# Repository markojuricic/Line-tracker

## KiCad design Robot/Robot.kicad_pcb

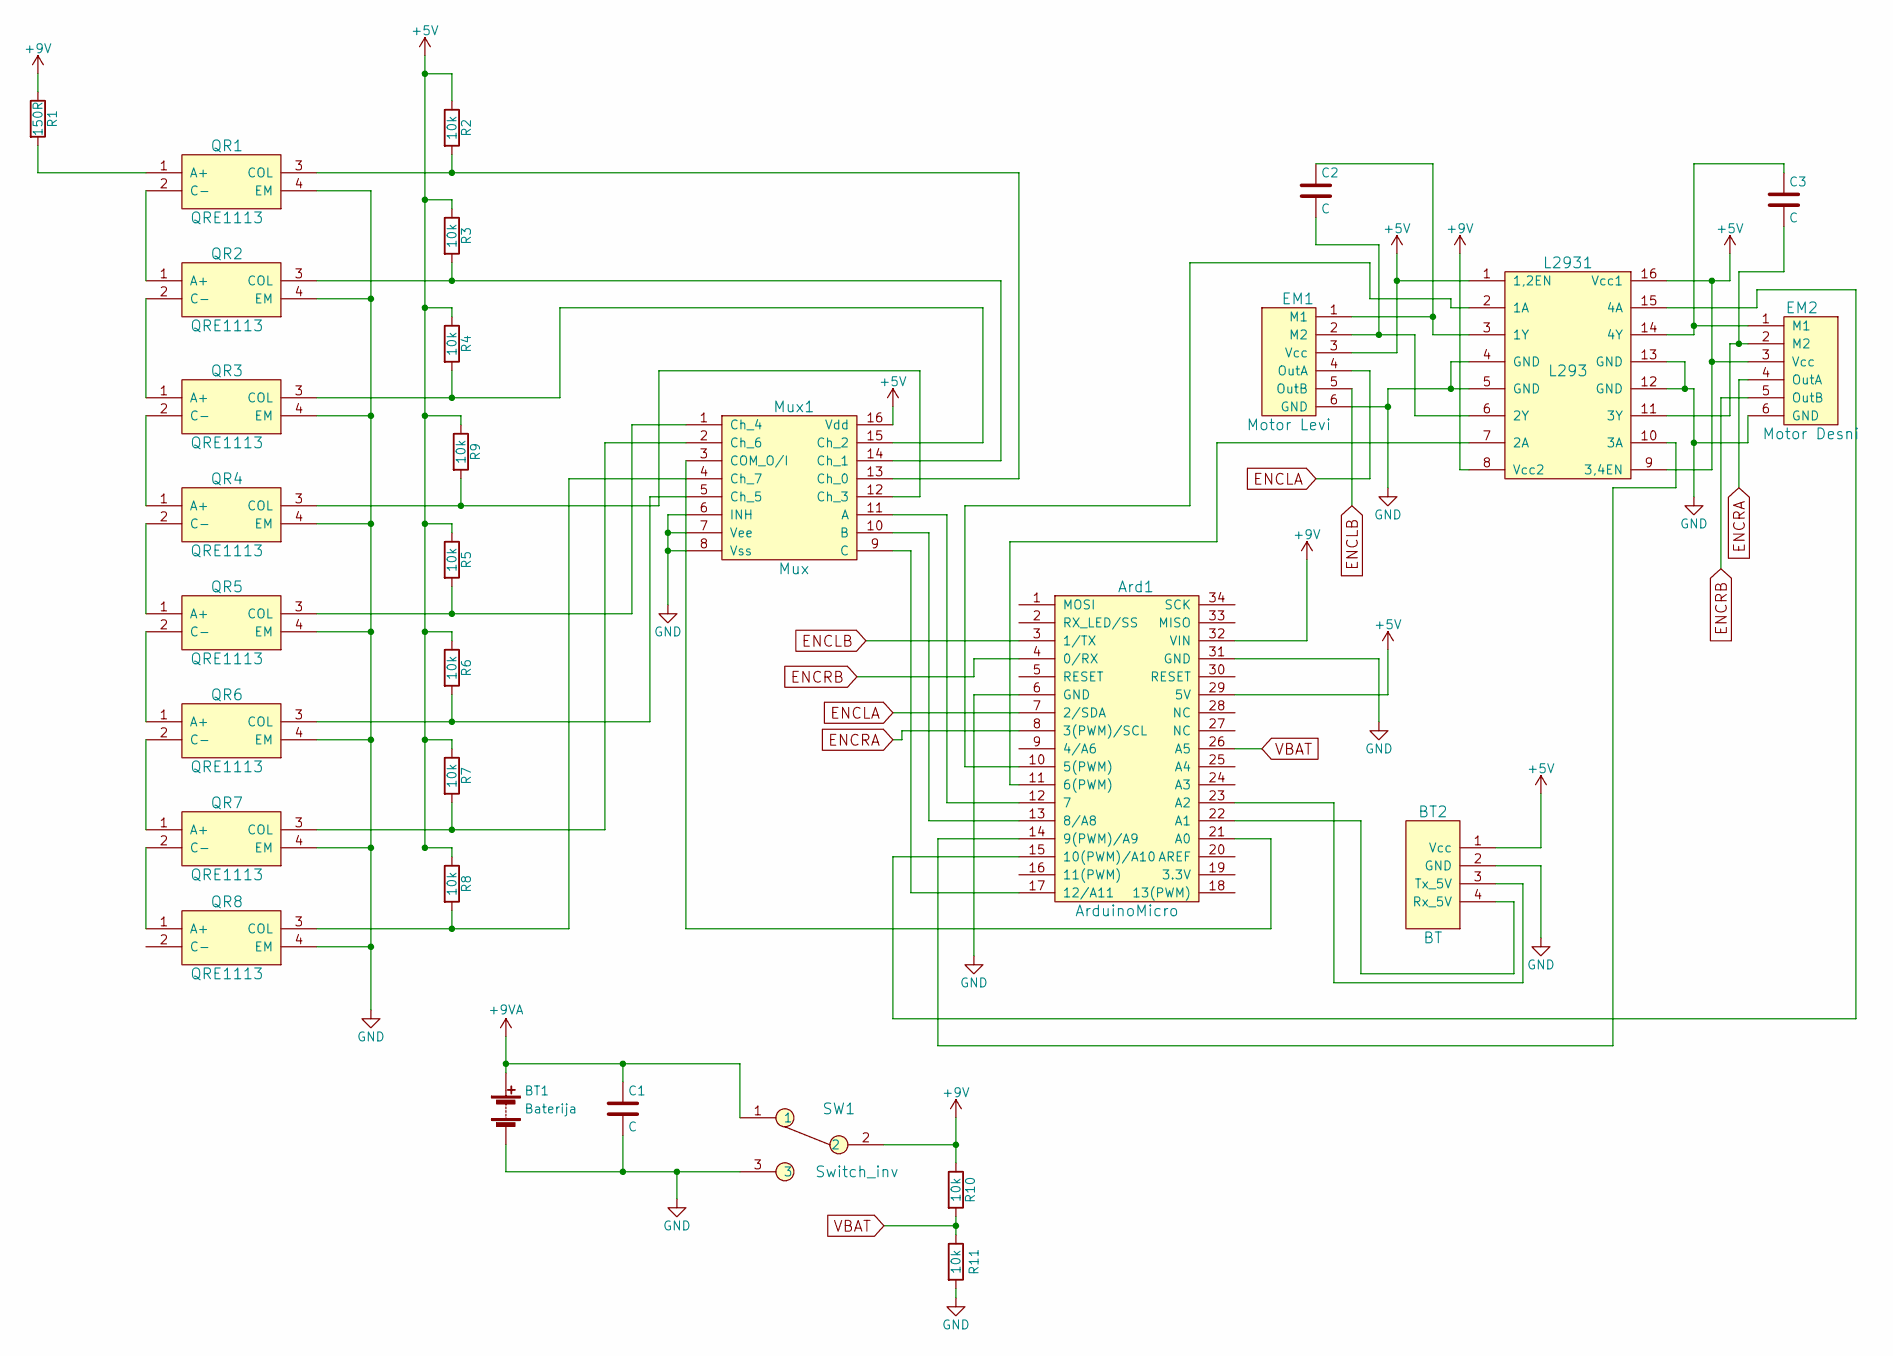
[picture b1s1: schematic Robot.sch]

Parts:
Ard1: ArduinoMicro; ARDUINO_MICRO_SHIELD
BT1: Baterija; Battery_holder_1291
BT2: BT; BT_Smirf
C1, C2, C3: C; C_0805_HandSoldering
EM1: Motor Levi; EM_holder
EM2: Motor Desni; EM_holder
L2931: L293
Mux1: Mux; Mux_8Ch
QR1, QR2, QR3, QR4, QR5, QR6, QR7, QR8: QRE1113; QRE1113GR
R1: 150R; R_0805_HandSoldering
R2, R3, R4, R5, R6, R7, R8, R9, R10, R11: 10k; R_0805_HandSoldering
SW1: Switch_inv; Switch

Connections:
+5V: Ard1.29 (5V), BT2.1 (Vcc), EM1.3 (Vcc), EM2.3 (Vcc), L2931.1 (1,2EN), L2931.9 (3,4EN), L2931.16 (Vcc1), Mux1.16 (Vdd), R2.1, R3.1, R4.1, R5.1, R6.1, R7.1, R8.1, R9.1
+9V: Ard1.32 (VIN), L2931.8 (Vcc2), R1.1, R10.1, SW1.2
+9VA: BT1.1 (+), C1.1, SW1.1
ENCLA: Ard1.7 (2/SDA), EM1.4 (OutA)
ENCLB: Ard1.3 (1/TX), EM1.5 (OutB)
ENCRA: Ard1.8 (3(PWM)/SCL), EM2.4 (OutA)
ENCRB: Ard1.4 (0/RX), EM2.5 (OutB)
GND: Ard1.6 (GND), Ard1.31 (GND), BT1.2 (-), BT2.2 (GND), C1.2, EM1.6 (GND), EM2.6 (GND), L2931.4 (GND), L2931.5 (GND), L2931.12 (GND), L2931.13 (GND), Mux1.6 (INH), Mux1.7 (Vee), Mux1.8 (Vss), QR1.4 (EM), QR2.4 (EM), QR3.4 (EM), QR4.4 (EM), QR5.4 (EM), QR6.4 (EM), QR7.4 (EM), QR8.4 (EM), R11.2, SW1.3
unnamed: Ard1.10 (5(PWM)), L2931.2 (1A)
unnamed: Ard1.11 (6(PWM)), L2931.7 (2A)
unnamed: Ard1.12 (7), Mux1.11 (A)
unnamed: Ard1.13 (8/A8), Mux1.10 (B)
unnamed: Ard1.14 (9(PWM)/A9), L2931.10 (3A)
unnamed: Ard1.15 (10(PWM)/A10), L2931.15 (4A)
unnamed: Ard1.17 (12/A11), Mux1.9 (C)
unnamed: Ard1.21 (A0), Mux1.3 (COM_O/I)
unnamed: Ard1.22 (A1), BT2.4 (Rx_5V)
unnamed: Ard1.23 (A2), BT2.3 (Tx_5V)
unnamed: C2.1, EM1.1 (M1), L2931.3 (1Y)
unnamed: C2.2, EM1.2 (M2), L2931.6 (2Y)
unnamed: C3.1, EM2.1 (M1), L2931.14 (4Y)
unnamed: C3.2, EM2.2 (M2), L2931.11 (3Y)
unnamed: Mux1.1 (Ch_4), QR5.3 (COL), R5.2
unnamed: Mux1.2 (Ch_6), QR7.3 (COL), R7.2
unnamed: Mux1.4 (Ch_7), QR8.3 (COL), R8.2
unnamed: Mux1.5 (Ch_5), QR6.3 (COL), R6.2
unnamed: Mux1.12 (Ch_3), QR4.3 (COL), R9.2
unnamed: Mux1.13 (Ch_0), QR1.3 (COL), R2.2
unnamed: Mux1.14 (Ch_1), QR2.3 (COL), R3.2
unnamed: Mux1.15 (Ch_2), QR3.3 (COL), R4.2
unnamed: QR1.1 (A+), R1.2
unnamed: QR1.2 (C-), QR2.1 (A+)
unnamed: QR2.2 (C-), QR3.1 (A+)
unnamed: QR3.2 (C-), QR4.1 (A+)
unnamed: QR4.2 (C-), QR5.1 (A+)
unnamed: QR5.2 (C-), QR6.1 (A+)
unnamed: QR6.2 (C-), QR7.1 (A+)
unnamed: QR7.2 (C-), QR8.1 (A+)
VBAT: Ard1.26 (A5), R10.2, R11.1

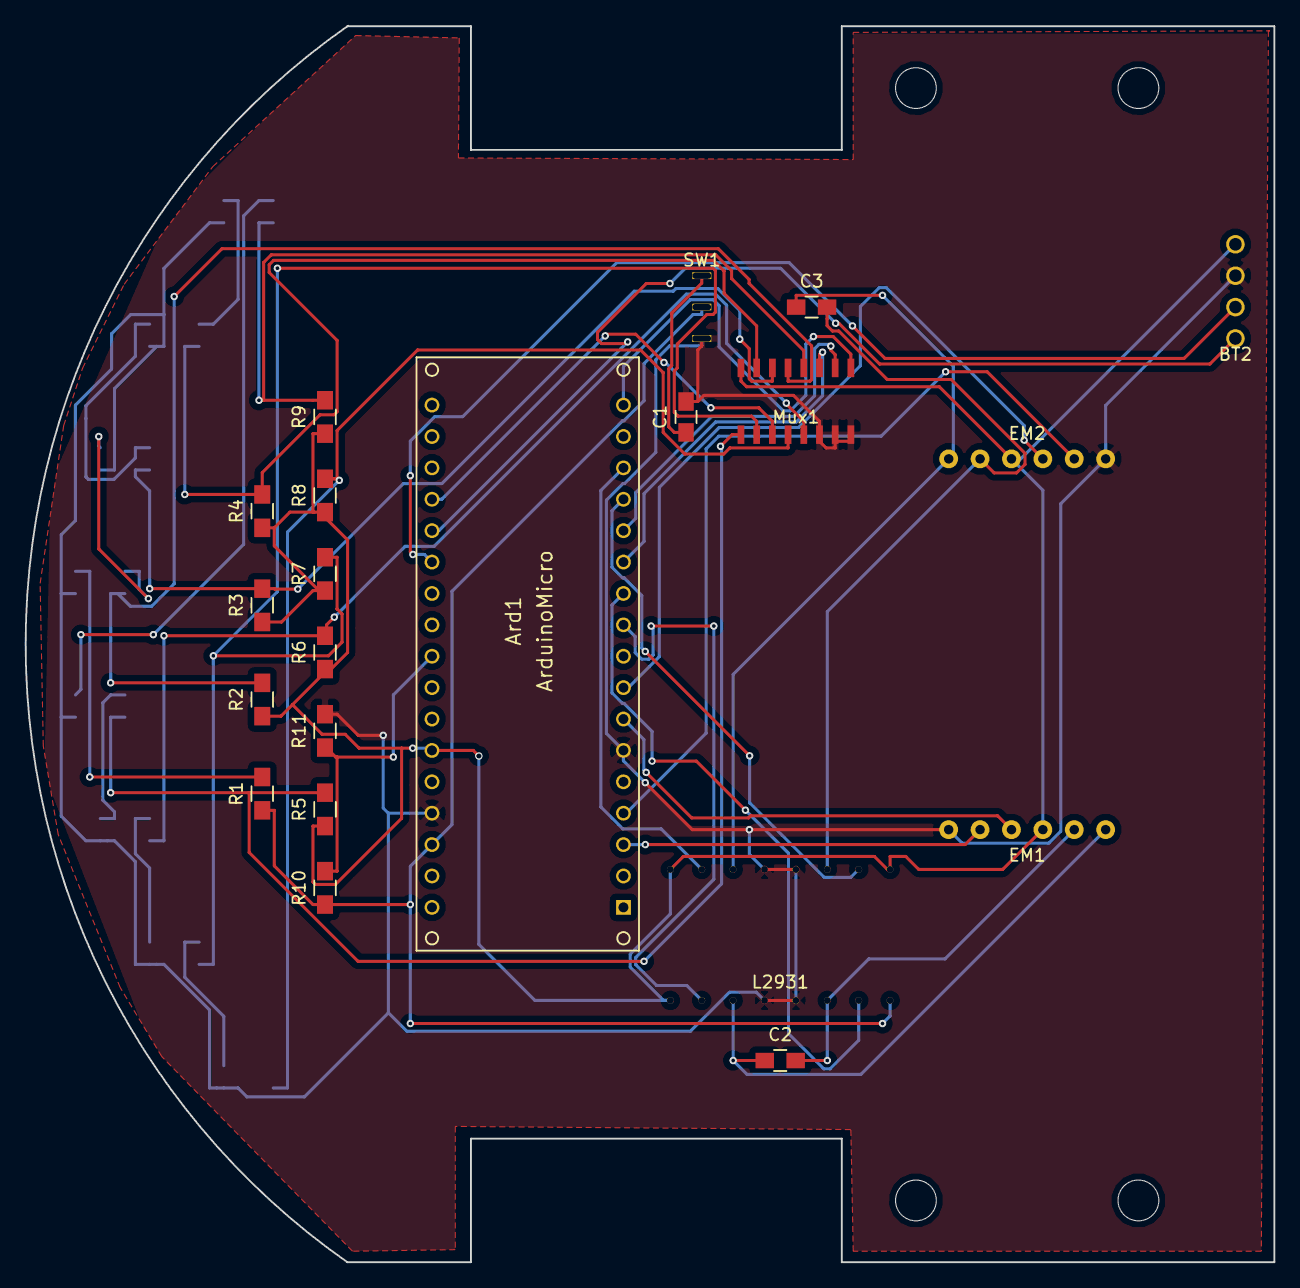
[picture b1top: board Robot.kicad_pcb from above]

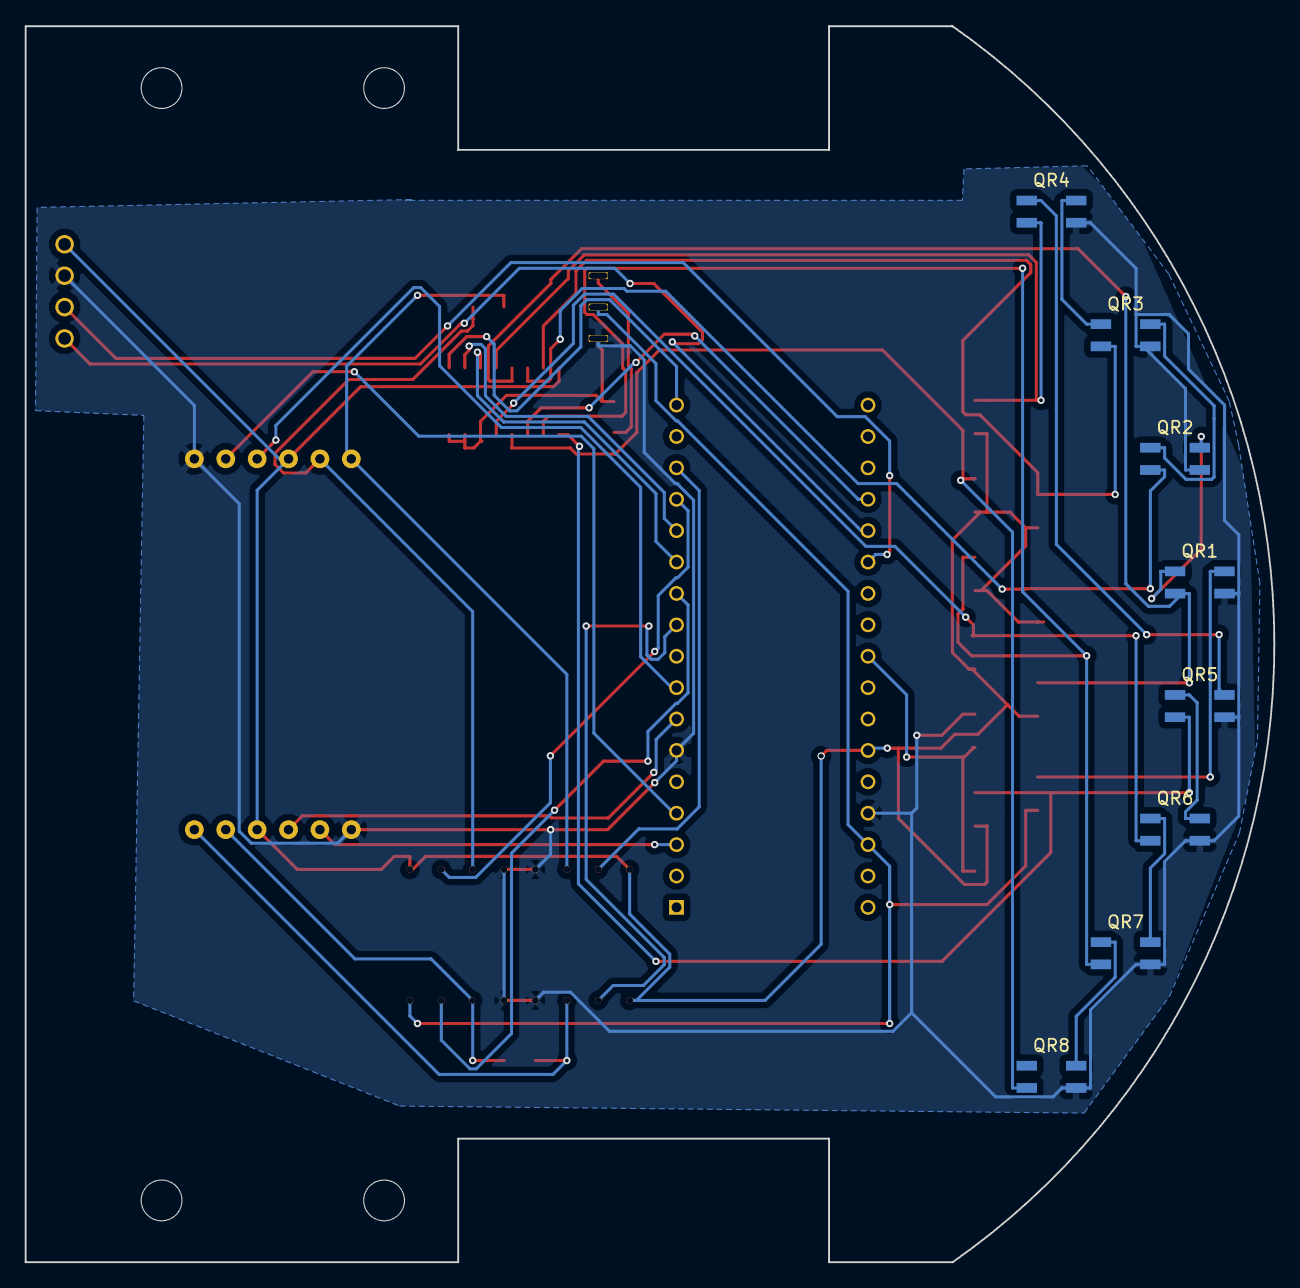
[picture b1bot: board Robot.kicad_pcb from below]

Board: 2 copper layers, 101.0 x 100.1 mm, 29 parts (8 on the bottom side), 39 nets.

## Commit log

2017-02-27 :circus_tent: Added .gitattributes
2017-02-27 KiCad projekt
2017-03-04 shema
    shema
2017-03-06 robot
2017-03-12 pdf
    pdf
2017-03-22 footprinti
